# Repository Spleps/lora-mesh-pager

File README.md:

# LoRa mesh-пейджер на власній друкованій платі

Науково-дослідна робота студента групи ЕЛ-12 Батрака Святослава.
Науковий керівник — Качурак Юрій Михайлович. Національний університет «Львівська політехніка», спеціальність G5 «Електроніка».

Текстовий пейджер для зв'язку малої групи без мобільної мережі й інтернету: повідомлення передаються радіо **LoRa на 433 МГц**,
пристрої утворюють **mesh-мережу** (кожен ретранслює чужі повідомлення). Ідея близька до Meshtastic, але апаратна частина —
**власна плата**: ESP32-S3 + голий чип SX1262 з усією обв'язкою, узгодженням і фільтром.

## Стан

| Частина | Стан |
|---|---|
| Принципова схема | готова, ERC — 0 помилок |
| Друкована плата | розведена (4 шари, 60 × 100 мм), DRC — 0 помилок, плата збігається зі схемою; Gerber і файл позицій готові |
| Номінали RF-узгодження | стартові значення розраховано; остаточні — після вимірювань NanoVNA |
| Виготовлення, прошивка | ще не розпочато |

## Що де лежить

| Папка | Вміст |
|---|---|
| [`hardware/v0.5`](hardware/v0.5/README.md) | **поточна версія** плати: проєкт KiCad, PDF схеми, Gerber, BOM, рендери, скрипти |
| [`hardware/v0.4`](hardware/v0.4/README.md) | попередня версія + її [аудит](hardware/v0.4/Аудит%20плати%20v0.4.md) |
| [`hardware/v0.6-plan`](hardware/v0.6-plan/Що%20додати%20в%20плату%20(v0.6).md) | що додати в наступну версію |
| [`docs/01-tema`](docs/01-tema) | пропозиція теми, дослідження по етапах |
| [`docs/02-doslidzhennia`](docs/02-doslidzhennia) | звіт дослідження (аналоги, публікації, розрахунки), джерела, симуляція mesh-мережі |
| [`docs/03-rozrakhunky-rf`](docs/03-rozrakhunky-rf/Стартові%20номінали%20RF%20433%20МГц.md) | розрахунок стартових номіналів радіотракту на 433 МГц |
| [`docs/literatura`](docs/literatura) | список використаних джерел (ДСТУ 8302:2015) |

## Версії плати

| Версія | Що змінилось |
|---|---|
| v0.1–v0.2 | перша схема; схему перемальовано «як вручну», з'єднання звірено нетлистом |
| v0.3 | повна перевірка; виправлено переплутані виводи 4 і 6 RF-ключа PE4259 |
| v0.4 | за джерелами Semtech: режектор 2-ї гармоніки, оновлений ФНЧ, кріпильні отвори |
| **v0.5** | за аудитом: розв'язка ESP32 впритул до виводу живлення, полігон 3,3 В, окреме живлення радіо через феритову намистину, RF-траса без перехідних |
| v0.6 | план: вібромотор, захист акумулятора, роз'єм розширення (ларингофон, GPS), тестові точки |

Кожна папка версії — окремий проєкт KiCad 10: відкривати `lora-pager.kicad_pro` всередині.

## Апаратна частина (v0.5)

- **Радіо:** SX1262 (QFN-24), DC-DC 15 мкГн, TCXO 32 МГц від DIO3, RF-ключ PE4259 від DIO2.
- **RF-тракт 433 МГц:** узгодження підсилювача → ФНЧ 5-го порядку → RF-ключ → LC-балун приймача → π-узгодження антени → SMA.
- **Мікроконтролер:** модуль ESP32-S3-WROOM-1-N16R8 (16 МБ flash, 8 МБ PSRAM, Wi-Fi/BLE, USB).
- **Живлення:** USB-C → заряд Li-ion MCP73831 → автоперемикання USB/батарея → LDO AP2112K-3.3.
- **Інтерфейс:** OLED SSD1306 128×64 (I2C), 3 кнопки, світлодіоди, UART.
- **Плата:** 4 шари (In1 — суцільна земля під RF), 1,6 мм, стек JLC04161H-7628.

## Потужність передавача

Відповідно до переліку радіочастот, що не потребують дозволу (постанова НКЕК № 361 від 03.07.2024, п. 50),
у смузі 433,05–434,79 МГц — 1 мВт ЕВП або до 10 мВт ЕВП при робочому циклі < 10 %.
Плата технічно підтримує до +22 dBm; у прошивці потужність обмежується до +10 dBm.

## Інструменти

KiCad 10, Python 3 + pcbnew API (скрипти в `hardware/*/tools`), Freerouting 2.5 для некритичних цифрових трас
(радіочастина й SPI біля SX1262 розведені вручну), NanoVNA — для налаштування RF (план).

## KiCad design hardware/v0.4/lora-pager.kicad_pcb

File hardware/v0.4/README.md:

# LoRa mesh-пейджер — принципова схема і друкована плата (KiCad 10)

Чернетка v0.4. Відкрити: `lora-pager.kicad_pro` у KiCad. Друк/перегляд: `lora-pager.pdf` (PNG: `lora-pager-schematic-1.png`).

**v0.4 — за первинними джерелами Semtech (AN1200.40, DS SX1268 рис. 14-1):**
- Додано C29 (DNP) паралельно L3 — місце під режектор 2-ї гармоніки, як C4 у схемі Semtech.
- ФНЧ: C17/C19 3,3 → 6,8 пФ, C18 10 → 12 пФ (котушки 22 нГн ті самі). Розрахункове послаблення 2-ї гармоніки 16 → 26 дБ, 3-ї 34 → 46 дБ.
- Додано 4 кріпильні отвори M2,5 без металізації (поза зоною антени модуля ESP32).
- Офіційних номіналів Semtech для 433 МГц у відкритому доступі немає (reference design лише 863–928 МГц) — «TBD 433» підбирати приладом.
  Балун за Semtech: L6 = 0 Ом, на місце C24 — котушка, C25 — конденсатор.
- Плата: DRC 0 помилок, 0 нерозведених, збігається зі схемою.

**v0.3 — повна перевірка проєкту, виправлено помилку:**
- **RF-ключ PE4259: у власному символі були переплутані виводи 4 і 6.** За даташитом pSemi (DOC-03694, табл. 5 і 7)
  вивід 4 = CTRL, вивід 6 = VDD. У v0.1–v0.2 на вивід 4 йшло 3,3 В, а DIO2 — на вивід 6: ключ завжди тримав би
  антену на TX-гілці й приймач не працював би. Тепер DIO2 → R15/C21 → вивід 4, +3V3 → R16/C22 → вивід 6.
  На платі R15/C21 і R16/C22 помінялись місцями, дві траси (DIO2 і відгалуження +3V3) перетрасовано.
- R5 (стягування затвора Q1) 100 кОм → 10 кОм: затвор швидше розряджається після відключення USB, і зворотний
  струм витоку D1 не може тримати Q1 закритим.
- На схемі й шовкографії додано полярність J2 («+», «−», BAT) і примітку про акумулятор із платою захисту.

**v0.2 — схему перемальовано «як руками»:** обв'язка (розв'язувальні C, RC на EN, підтяжки, LED, UART, TCXO, DC-DC)
стоїть біля виводів своєї мікросхеми й з'єднана проводами; мітки лишились тільки на зв'язках між блоками
(SPI/DIO до SX1262, I2C, USB, кнопки, RF-сигнали) та на вузлах RF-тракту. Справа внизу — легенда
(перекреслені елементи = DNP, не паяти). З'єднання v0.2 ті самі, що у v0.1 (звірено нетлистом, 76 цепей).
Перелік елементів: `BOM_draft.csv`. Схему згенеровано скриптом `tools/gen_sch.py`
(`python3 tools/gen_sch.py .` перезапише схему — ручні правки в KiCad тоді зітруться).

ERC: 0 помилок, 1 очікуване попередження (живлення TCXO від виводу DIO3 SX1262).

## Блоки
1. **Живлення**: USB-C (5,1 кОм на CC1/CC2), ESD USBLC6-2SC6, заряд Li-ion MCP73831 (500 мА, R3 = 2 кОм),
   автоперемикання USB/батарея (D1 B5819W + P-MOSFET Q1 AO3401A), вимикач SW1, LDO AP2112K-3.3 (600 мА),
   дільник батареї 1:2 на ADC.
2. **MCU**: ESP32-S3-WROOM-1-N16R8, нативний USB (D+/D-), кнопки RESET/BOOT, UART-роз'єм, зелений LED.
3. **Дисплей**: модуль OLED SSD1306 128×64 I2C (4 виводи). Порядок GND/VCC/SCL/SDA звірити з модулем.
4. **Радіо**: голий SX1262 (QFN-24), DC-DC з дроселем 15 мкГн, VREG 470 нФ, TCXO 32 МГц (TG2520SMN) з
   живленням від DIO3 через 220 Ом + 10 пФ на XTA (за Semtech DS v2.2, рис. 4-2 та 14-2).
5. **RF-тракт 433 МГц**: дросель PA, узгодження PA, ФНЧ 5-го порядку, RF-ключ PE4259 у single-pin режимі
   (вив. 6 VDD = 3,3 В; вив. 4 CTRL ← DIO2: 1 = TX, RFC–RF1; 0 = RX, RFC–RF2), LC-балун приймача, π-узгодження антени, SMA.

## GPIO ESP32-S3
| Сигнал | GPIO | | Сигнал | GPIO |
|---|---|---|---|---|
| LORA_NSS | 10 | | OLED_SDA | 17 |
| LORA_MOSI | 11 | | OLED_SCL | 18 |
| LORA_SCK | 12 | | BTN_UP / DOWN / OK | 4 / 5 / 6 |
| LORA_MISO | 13 | | BAT_ADC | 1 (ADC1_CH0) |
| LORA_BUSY | 14 | | LED_STAT | 2 |
| LORA_DIO1 (IRQ) | 9 | | USB D- / D+ | 19 / 20 |
| LORA_NRST | 8 | | UART TX / RX | 43 / 44 |

Не використано ножки-«страпи» GPIO0/3/45/46 (крім кнопки BOOT на GPIO0) і GPIO35–37 (зайняті PSRAM у N16R8).

## Що ще НЕ готово (обов'язково до замовлення плати)
- **Номінали RF з позначкою `TBD 433`** (L3, C29, C24, L6, C25, L7, C27, C28) — узгодження PA, режектор 2-ї гармоніки, балун RX і антена.
  Підбирати векторним аналізатором (NanoVNA): офіційні reference design Semtech є лише для 863–928 МГц (AN1200.40, табл. 1),
  проєкт для 433 МГц можна запросити в представника Semtech. Елементи з хрестиком = DNP.
- ФНЧ (C17 6,8 пФ, L4 22 нГн, C18 12 пФ, L5 22 нГн, C19 6,8 пФ; конденсатори C0G 2 %) — власний розрахунок, близький до Чебишева 0,1 дБ
  зі зрізом ≈500 МГц, 50 Ом. Вихідний опір PA не 50 Ом, тому після узгодження перевірити спектр гармонік.
- Розрахункове послаблення ФНЧ (ідеальні елементи): 2-га гармоніка (868 МГц) — 26 дБ, 3-тя — 46 дБ; втрати на 434 МГц ≈ 0,6 дБ з реальною добротністю.
  Якщо цього замало — поставити режектор C29 паралельно L3 (резонанс C29–L3 на 868 МГц, як C4 у Semtech AN1200.40, п. 3.1.3).
- У прошивці обов'язково викликати `SetDIO2AsRfSwitchCtrl` — інакше ключ лишиться в положенні RX.
- TCXO: напругу в `SetDIO3AsTCXOCtrl` задати під конкретний TCXO (1,8 В для TG2520SMN-…NM), VBAT ≥ VTCXO + 200 мВ.
- Потужність: в Україні SRD 433,05–434,79 МГц — 1 мВт ЕВП без обмеження робочого циклу або до 10 мВт ЕВП при робочому циклі < 10 % (постанова НКЕК № 361 від 03.07.2024, п. 50, рядок 101; антена «інтегрована/конструктивна»). Не вмикати +22 dBm без дозволу/вимірювань.
- Footprint-и пасивів 0603; для RF можна 0402. Під SX1262 — via під exposed pad, суцільна земля під RF.

## Обмеження конструкції (знати до складання)
- **Акумулятор — тільки із вбудованою платою захисту (PCM).** На платі немає захисту від перерозряду й короткого замикання.
- **Полярність J2 (JST-PH): вивід 1 = «+», вивід 2 = GND.** У готових акумуляторів дроти бувають навпаки — звірити до підключення;
  захисту від переполюсовки немає.
- Заряд 500 мА (R3 = 2 кОм) плюс живлення плати від того ж USB можуть перевищити 500 мА порту USB 2.0; для слабких портів
  і акумуляторів менше 500 мА·год поставити R3 = 3,3–10 кОм (300–100 мА).
- Вимикач SW1 керує входом EN стабілізатора: у вимкненому стані від батареї лишається лише дільник R7/R8 (≈20 мкА).
- Кріпильні отвори M2,5 (без металізації): три в кутах і один біля SMA, усі поза зоною антени ESP32. Біля антени краще пластикові гвинти/стійки.
- 3V3 провалюється, коли батарея нижче ≈3,5 В при великому струмі (падіння на Q1 і LDO) — це нормальна межа розряду.

## Друкована плата v0.4 — розведена
- `lora-pager.kicad_pcb`: 60 × 100 мм, 4 шари, 1,6 мм (JLC04161H-7628):
  F.Cu сигнали + GND-заливка, **In1 = суцільна GND** (опора для RF), In2 = сигнали та +3V3, B.Cu сигнали + GND-заливка.
- **DRC: 0 помилок, 0 нерозведених, плата збігається зі схемою.** Лишились тільки 28 попереджень шовкографії (написи на площадках).
- Класи: Default 0,2 мм / via 0,45/0,2; Power 0,4 мм / via 0,7/0,35; RF 0,35 мм. Біля виводів QFN траси звужуються до 0,12–0,25 мм.
- Виводи SX1262 розведено вручну й закріплено (SPI — два ряди via, RFO/RFI_P/RFI_N короткими трасами, 4 тепловідвідні via),
  решту — Freerouting. ~380 GND-via зшивають заливки з In1.
- Виробництво: `lora-pager-gerbers.zip` (Gerber + свердління), `fab/lora-pager-pos.csv` (координати для монтажу), рендери в `renders/`.

### Як перезібрати
```bash
kicad-cli sch export netlist --format kicadsexpr -o /tmp/pager.net lora-pager.kicad_sch
python3 tools/gen_pcb.py /tmp/pager.net     # розміщення, шари, правила, ручна розводка U2
PASSES=100 tools/route.sh                   # Freerouting -> імпорт -> прибирання хвостів -> зшивка GND
kicad-cli pcb drc --refill-zones --schematic-parity lora-pager.kicad_pcb
```
Якщо змінився лише вигляд схеми, номінали чи примітки (не з'єднання) — плату не перетрасовувати:
```bash
kicad-cli sch export netlist --format kicadsexpr -o route/sch.net lora-pager.kicad_sch
python3 tools/sync_pcb.py                   # нові UUID символів, імена цепей, номінали й примітки; траси без змін
```
Невелика зміна з'єднань: зняти зачеплені траси, оновити цепи площадок і запустити `tools/finish_route.sh`
(дотрасування поверх наявної плати). Приклад — `tools/eco_u6_fix.py` (виправлення PE4259 у v0.3). Додавання елементів без перетрасування —
`tools/eco_v04.py` (C29 і кріпильні отвори у v0.4).
Скрипти перезаписують плату — ручні правки в KiCad після цього зітруться.

### Перед замовленням перевірити
- Номінали RF «TBD 433» (див. вище) і що SMA/антена — 50 Ом.
- Вирівняти написи шовкографії (косметика) та перевірити в KiCad 3D з моделями (на ноутбуці 3D-моделей немає).
- Дросель L1 LPS3010 — наявність; OLED-модуль — порядок виводів GND/VCC/SCL/SDA.

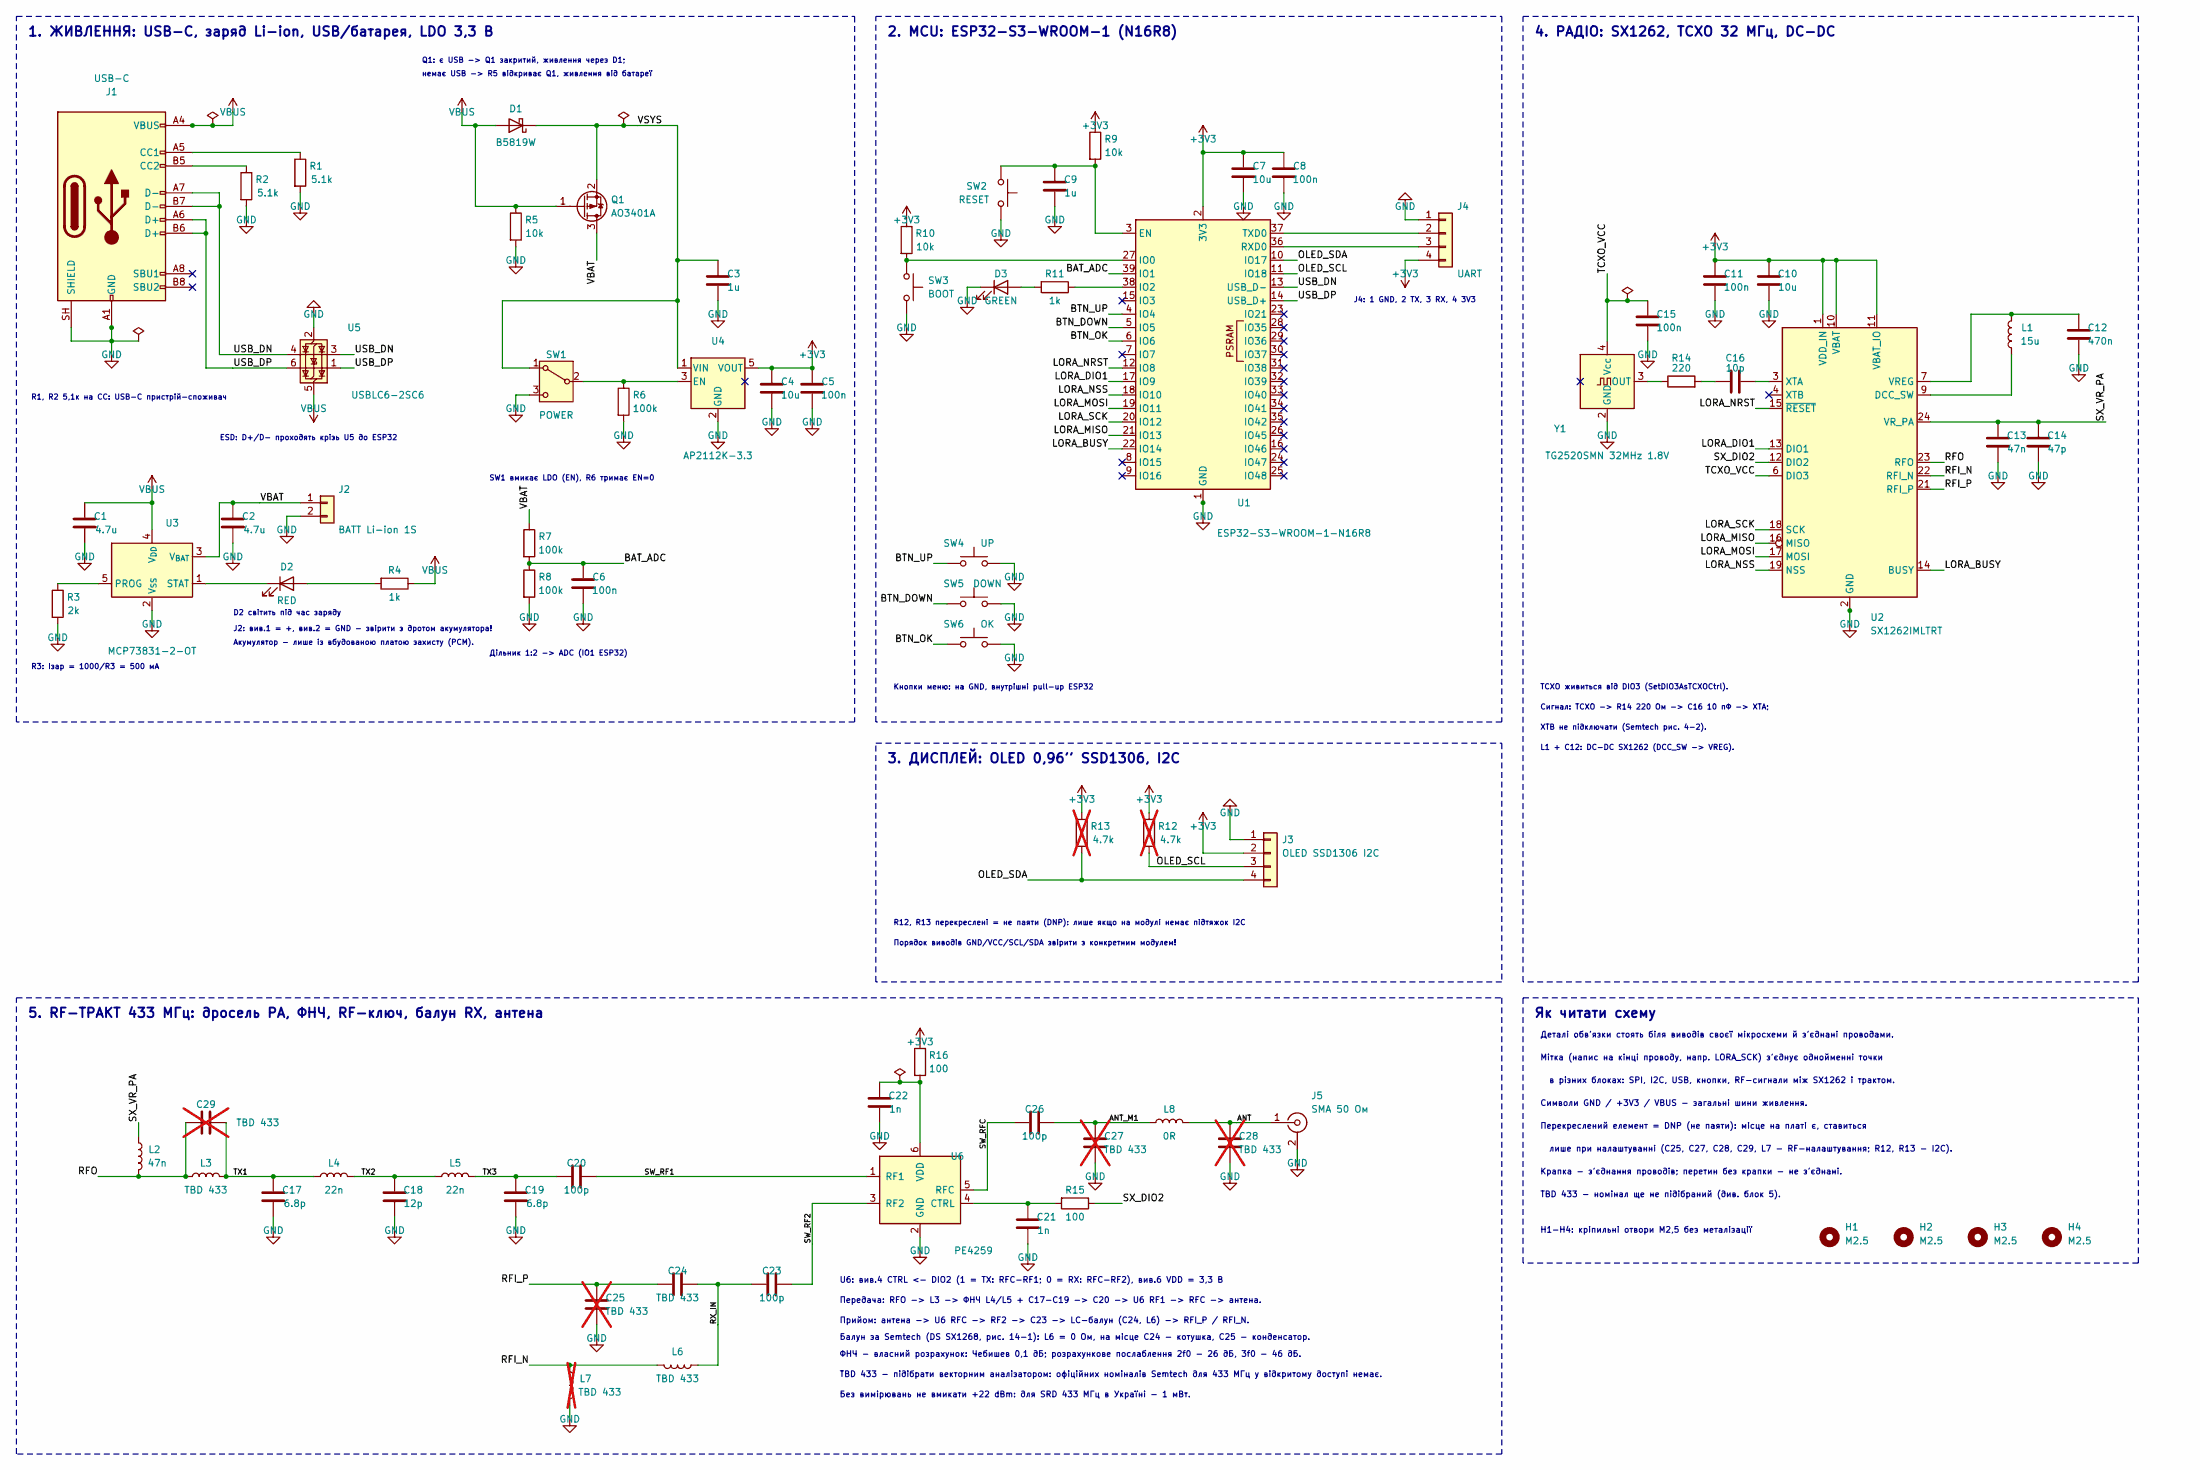
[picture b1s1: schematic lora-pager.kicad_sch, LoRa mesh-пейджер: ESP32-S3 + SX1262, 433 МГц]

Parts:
C1, C2: 4.7u; C_0805_2012Metric
C3, C9: 1u; C_0603_1608Metric
C4, C7, C10: 10u; C_0805_2012Metric
C5, C6, C8, C11, C15: 100n; C_0603_1608Metric
C12: 470n; C_0603_1608Metric
C13: 47n; C_0603_1608Metric
C14: 47p; C_0603_1608Metric
C16: 10p; C_0603_1608Metric
C17, C19: 6.8p; C_0603_1608Metric
C18: 12p; C_0603_1608Metric
C20, C23, C26: 100p; C_0603_1608Metric
C21, C22: 1n; C_0603_1608Metric
C24: TBD 433; C_0603_1608Metric
C25, C27, C28, C29: TBD 433; C_0603_1608Metric; not fitted
D1: B5819W; D_SOD-123
D2: RED; LED_0603_1608Metric
D3: GREEN; LED_0603_1608Metric
H1, H2, H3, H4: M2.5; MountingHole_2.7mm_M2.5
J1: USB-C; USB_C_Receptacle_HRO_TYPE-C-31-M-12
J2: BATT Li-ion 1S; JST_PH_S2B-PH-K_1x02_P2.00mm_Horizontal
J3: OLED SSD1306 I2C; PinHeader_1x04_P2.54mm_Vertical
J4: UART; PinHeader_1x04_P2.54mm_Vertical
J5: SMA 50 Ом; SMA_Amphenol_132289_EdgeMount
L1: 15u; L_Coilcraft_LPS3010
L2: 47n; L_0603_1608Metric
L3, L6: TBD 433; L_0603_1608Metric
L4, L5: 22n; L_0603_1608Metric
L7: TBD 433; L_0603_1608Metric; not fitted
L8: 0R; L_0603_1608Metric
Q1: AO3401A; SOT-23
R1, R2: 5.1k; R_0603_1608Metric
R3: 2k; R_0603_1608Metric
R4, R11: 1k; R_0603_1608Metric
R5, R9, R10: 10k; R_0603_1608Metric
R6, R7, R8: 100k; R_0603_1608Metric
R12, R13: 4.7k; R_0603_1608Metric; not fitted
R14: 220; R_0603_1608Metric
R15, R16: 100; R_0603_1608Metric
SW1: POWER; SW_SPDT_PCM12
SW2: RESET; SW_SPST_TL3342
SW3: BOOT; SW_SPST_TL3342
SW4: UP; SW_SPST_TL3342
SW5: DOWN; SW_SPST_TL3342
SW6: OK; SW_SPST_TL3342
U1: ESP32-S3-WROOM-1-N16R8; ESP32-S3-WROOM-1
U2: SX1262IMLTRT; QFN-24-1EP_4x4mm_P0.5mm_EP2.6x2.6mm
U3: MCP73831-2-OT; SOT-23-5
U4: AP2112K-3.3; SOT-23-5
U5: USBLC6-2SC6; SOT-23-6
U6: PE4259; SOT-363_SC-70-6
Y1: TG2520SMN 32MHz 1.8V; Oscillator_SMD_SeikoEpson_TG2520SMN-xxx-xxxxxx-4Pin_2.5x2.0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

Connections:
+3V3: C4.1, C5.1, C7.1, C8.1, C10.1, C11.1, J3.2, J4.4, R9.1, R10.1, R12.1, R13.1, R16.1, U1.2 (3V3), U2.1 (VDD_IN), U2.10 (VBAT), U2.11 (VBAT_IO), U4.5 (VOUT)
/ANT: C28.1, J5.1 (In), L8.2
/ANT_M1: C26.2, C27.1, L8.1
/BAT_ADC: C6.1, R7.2, R8.1, U1.39 (IO1)
/BTN_DOWN: SW5.1, U1.5 (IO5)
/BTN_OK: SW6.1, U1.6 (IO6)
/BTN_UP: SW4.1, U1.4 (IO4)
/LORA_BUSY: U1.22 (IO14), U2.14 (BUSY)
/LORA_DIO1: U1.17 (IO9), U2.13 (DIO1)
/LORA_MISO: U1.21 (IO13), U2.16 (MISO)
/LORA_MOSI: U1.19 (IO11), U2.17 (MOSI)
/LORA_NRST: U1.12 (IO8), U2.15 (~RESET)
/LORA_NSS: U1.18 (IO10), U2.19 (NSS)
/LORA_SCK: U1.20 (IO12), U2.18 (SCK)
/OLED_SCL: J3.3, R12.2, U1.11 (IO18)
/OLED_SDA: J3.4, R13.2, U1.10 (IO17)
/RFI_N: L6.2, L7.1, U2.22 (RFI_N)
/RFI_P: C24.2, C25.1, U2.21 (RFI_P)
/RFO: C29.1, L2.2, L3.1, U2.23 (RFO)
/RX_IN: C23.2, C24.1, L6.1
/SW_RF1: C20.2, U6.1 (RF1)
/SW_RF2: C23.1, U6.3 (RF2)
/SW_RFC: C26.1, U6.5 (RFC)
/SX_DIO2: R15.1, U2.12 (DIO2)
/SX_VR_PA: C13.1, C14.1, L2.1, U2.24 (VR_PA)
/TCXO_VCC: C15.1, U2.6 (DIO3), Y1.4 (Vcc)
/TX1: C17.1, C29.2, L3.2, L4.1
/TX2: C18.1, L4.2, L5.1
/TX3: C19.1, C20.1, L5.2
/USB_DN: J1.A7 (D-), J1.B7 (D-), U1.13 (USB_D-), U5.3 (I/O2), U5.4 (I/O2)
/USB_DP: J1.A6 (D+), J1.B6 (D+), U1.14 (USB_D+), U5.1 (I/O1), U5.6 (I/O1)
/VBAT: C2.1, J2.1, Q1.3 (D), R7.1, U3.3 (V_{BAT})
/VSYS: C3.1, D1.1 (K), Q1.2 (S), SW1.1 (A), U4.1 (VIN)
GND: C1.2, C2.2, C3.2, C4.2, C5.2, C6.2, C7.2, C8.2, C9.2, C10.2, C11.2, C12.2, C13.2, C14.2, C15.2, C17.2, C18.2, C19.2, C21.2, C22.2, C25.2, C27.2, C28.2, D3.1 (K), J1.A1 (GND), J1.A12 (GND), J1.B1 (GND), J1.B12 (GND), J1.SH (SHIELD), J2.2, J3.1, J4.1, J5.2 (Ext), L7.2, R1.2, R2.2, R3.2, R5.2, R6.2, R8.2, SW1.3 (C), SW2.2, SW3.2, SW4.2, SW5.2, SW6.2, U1.1 (GND), U1.40 (GND), U1.41 (GND), U2.2 (GND), U2.5 (GND), U2.8 (GND), U2.20 (GND), U2.25 (GND), U3.2 (V_{SS}), U4.2 (GND), U5.2 (GND), U6.2 (GND), Y1.2 (GND)
unnamed: C16.1, R14.2
unnamed: D2.2 (A), R4.2
unnamed: D2.1 (K), U3.1 (STAT)
unnamed: D3.2 (A), R11.2
unnamed: J1.A5 (CC1), R1.1
unnamed: J1.B5 (CC2), R2.1
unnamed: J4.2, U1.37 (TXD0)
unnamed: J4.3, U1.36 (RXD0)
unnamed: R6.1, SW1.2 (B), U4.3 (EN)
unnamed: C9.1, R9.2, SW2.1, U1.3 (EN)
unnamed: R10.2, SW3.1, U1.27 (IO0)
unnamed: R11.1, U1.38 (IO2)
unnamed: L1.1, U2.9 (DCC_SW)
unnamed: C12.1, L1.2, U2.7 (VREG)
unnamed: C16.2, U2.3 (XTA)
unnamed: R3.1, U3.5 (PROG)
unnamed: C21.1, R15.2, U6.4 (CTRL)
unnamed: C22.1, R16.2, U6.6 (VDD)
unnamed: R14.1, Y1.3 (OUT)
VBUS: C1.1, D1.2 (A), J1.A4 (VBUS), J1.A9 (VBUS), J1.B4 (VBUS), J1.B9 (VBUS), Q1.1 (G), R4.1, R5.1, U3.4 (V_{DD}), U5.5 (VBUS)

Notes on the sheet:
1. ЖИВЛЕННЯ: USB-C, заряд Li-ion, USB/батарея, LDO 3,3 В
ESD: D+/D- проходять крізь U5 до ESP32
R1, R2 5,1к на CC: USB-C пристрій-споживач
D2 світить під час заряду
J2: вив.1 = +, вив.2 = GND - звірити з дротом акумулятора!
Акумулятор - лише із вбудованою платою захисту (PCM).
R3: Iзар = 1000/R3 = 500 мА
Q1: є USB -> Q1 закритий, живлення через D1;
немає USB -> R5 відкриває Q1, живлення від батареї
U6: вив.4 CTRL <- DIO2 (1 = TX: RFC-RF1; 0 = RX: RFC-RF2), вив.6 VDD = 3,3 В
SW1 вмикає LDO (EN), R6 тримає EN=0
Дільник 1:2 -> ADC (IO1 ESP32)
2. MCU: ESP32-S3-WROOM-1 (N16R8)
J4: 1 GND, 2 TX, 3 RX, 4 3V3
Кнопки меню: на GND, внутрішні pull-up ESP32
3. ДИСПЛЕЙ: OLED 0,96'' SSD1306, I2C
R12, R13 перекреслені = не паяти (DNP): лише якщо на модулі немає підтяжок I2C
Порядок виводів GND/VCC/SCL/SDA звірити з конкретним модулем!
4. РАДІО: SX1262, TCXO 32 МГц, DC-DC
TCXO живиться від DIO3 (SetDIO3AsTCXOCtrl).
Сигнал: TCXO -> R14 220 Ом -> C16 10 пФ -> XTA;
XTB не підключати (Semtech рис. 4-2).
L1 + C12: DC-DC SX1262 (DCC_SW -> VREG).
5. RF-ТРАКТ 433 МГц: дросель PA, ФНЧ, RF-ключ, балун RX, антена
Передача: RFO -> L3 -> ФНЧ L4/L5 + C17-C19 -> C20 -> U6 RF1 -> RFC -> антена.
Прийом: антена -> U6 RFC -> RF2 -> C23 -> LC-балун (C24, L6) -> RFI_P / RFI_N.
Балун за Semtech (DS SX1268, рис. 14-1): L6 = 0 Ом, на місце C24 - котушка, C25 - конденсатор.
ФНЧ - власний розрахунок: Чебишев 0,1 дБ; розрахункове послаблення 2f0 - 26 дБ, 3f0 - 46 дБ.
TBD 433 - підібрати векторним аналізатором: офіційних номіналів Semtech для 433 МГц у відкритому доступі немає.
Без вимірювань не вмикати +22 dBm: для SRD 433 МГц в Україні - 1 мВт.
Як читати схему
Деталі обв'язки стоять біля виводів своєї мікросхеми й з'єднані проводами.
Мітка (напис на кінці проводу, напр. LORA_SCK) з'єднує однойменні точки
в різних блоках: SPI, I2C, USB, кнопки, RF-сигнали між SX1262 і трактом.
Символи GND / +3V3 / VBUS - загальні шини живлення.
Перекреслений елемент = DNP (не паяти): місце на платі є, ставиться
лише при налаштуванні (C25, C27, C28, C29, L7 - RF-налаштування; R12, R13 - I2C).
Крапка - з'єднання проводів; перетин без крапки - не з'єднані.
TBD 433 - номінал ще не підібраний (див. блок 5).
H1-H4: кріпильні отвори M2,5 без металізації

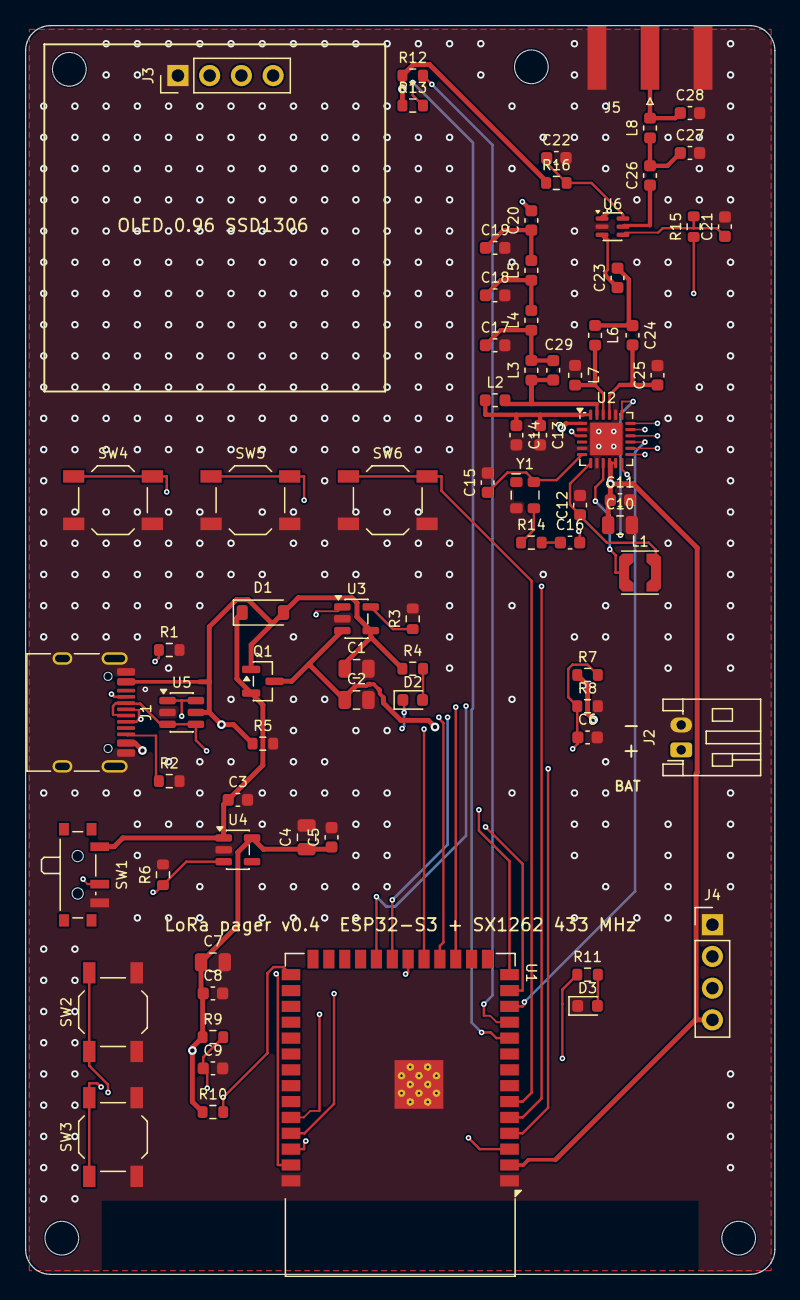
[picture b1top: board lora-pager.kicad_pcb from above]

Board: 4 copper layers, 60.0 x 100.0 mm, 79 parts (0 on the bottom side), 54 nets.

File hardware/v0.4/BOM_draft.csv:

Ref,Value,Footprint,Note
C1,4.7u,Capacitor_SMD:C_0805_2012Metric,
C2,4.7u,Capacitor_SMD:C_0805_2012Metric,
C3,1u,Capacitor_SMD:C_0603_1608Metric,
C4,10u,Capacitor_SMD:C_0805_2012Metric,
C5,100n,Capacitor_SMD:C_0603_1608Metric,
C6,100n,Capacitor_SMD:C_0603_1608Metric,
C7,10u,Capacitor_SMD:C_0805_2012Metric,
C8,100n,Capacitor_SMD:C_0603_1608Metric,
C9,1u,Capacitor_SMD:C_0603_1608Metric,
C10,10u,Capacitor_SMD:C_0805_2012Metric,
C11,100n,Capacitor_SMD:C_0603_1608Metric,біля VBAT/VBAT_IO (Semtech C18)
C12,470n,Capacitor_SMD:C_0603_1608Metric,Semtech C17
C13,47n,Capacitor_SMD:C_0603_1608Metric,
C14,47p,Capacitor_SMD:C_0603_1608Metric,
C15,100n,Capacitor_SMD:C_0603_1608Metric,
C16,10p,Capacitor_SMD:C_0603_1608Metric,
C17,6.8p,Capacitor_SMD:C_0603_1608Metric,"ФНЧ 5 порядку (Чебишев 0,1 дБ, зріз ~500 МГц, 50 Ом), C0G 2%; власний розрахунок"
C18,12p,Capacitor_SMD:C_0603_1608Metric,"ФНЧ, C0G 2%"
C19,6.8p,Capacitor_SMD:C_0603_1608Metric,"ФНЧ, C0G 2%"
C20,100p,Capacitor_SMD:C_0603_1608Metric,розділовий
C21,1n,Capacitor_SMD:C_0603_1608Metric,Semtech C15
C22,1n,Capacitor_SMD:C_0603_1608Metric,Semtech C14
C23,100p,Capacitor_SMD:C_0603_1608Metric,розділовий
C24,TBD 433,Capacitor_SMD:C_0603_1608Metric,LC-балун RX: підбір під 433 МГц
C25,TBD 433,Capacitor_SMD:C_0603_1608Metric,LC-балун RX
C26,100p,Capacitor_SMD:C_0603_1608Metric,розділовий
C27,TBD 433,Capacitor_SMD:C_0603_1608Metric,π-узгодження антени
C28,TBD 433,Capacitor_SMD:C_0603_1608Metric,π-узгодження антени
C29,TBD 433,Capacitor_SMD:C_0603_1608Metric,"режектор 2-ї гармоніки: C29 || L3 резонує на 2f0 = 868 МГц (як C4 у Semtech AN1200.40, п. 3.1.3)"
D1,B5819W,Diode_SMD:D_SOD-123,
D2,RED,LED_SMD:LED_0603_1608Metric,
D3,GREEN,LED_SMD:LED_0603_1608Metric,
J1,USB-C,Connector_USB:USB_C_Receptacle_HRO_TYPE-C-31-M-12,
J2,BATT Li-ion 1S,Connector_JST:JST_PH_S2B-PH-K_1x02_P2.00mm_Horizontal,
J3,OLED SSD1306 I2C,Connector_PinHeader_2.54mm:PinHeader_1x04_P2.54mm_Vertical,
J4,UART,Connector_PinHeader_2.54mm:PinHeader_1x04_P2.54mm_Vertical,
J5,SMA 50 Ом,Connector_Coaxial:SMA_Amphenol_132289_EdgeMount,
L1,15u,Inductor_SMD:L_Coilcraft_LPS3010,"LPS3010-153, DCR<=2 Ом, Idc>=100 мА (Semtech 5.1.5)"
L2,47n,Inductor_SMD:L_0603_1608Metric,дросель живлення PA (як L8 у DATALOGGER02); перевірити для 433
L3,TBD 433,Inductor_SMD:L_0603_1608Metric,"узгодження PA, підбір NanoVNA/за ref-design 433-490"
L4,22n,Inductor_SMD:L_0603_1608Metric,ФНЧ
L5,22n,Inductor_SMD:L_0603_1608Metric,ФНЧ
L6,TBD 433,Inductor_SMD:L_0603_1608Metric,LC-балун RX
L7,TBD 433,Inductor_SMD:L_0603_1608Metric,LC-балун RX
L8,0R,Inductor_SMD:L_0603_1608Metric,π-узгодження: перемичка 0 Ом до налаштування
Q1,AO3401A,Package_TO_SOT_SMD:SOT-23,
R1,5.1k,Resistor_SMD:R_0603_1608Metric,
R2,5.1k,Resistor_SMD:R_0603_1608Metric,
R3,2k,Resistor_SMD:R_0603_1608Metric,Iзар = 1000/R = 500 мА
R4,1k,Resistor_SMD:R_0603_1608Metric,
R5,10k,Resistor_SMD:R_0603_1608Metric,"стягує затвор Q1; 10k, щоб зворотний струм витоку D1 не тримав Q1 закритим"
R6,100k,Resistor_SMD:R_0603_1608Metric,
R7,100k,Resistor_SMD:R_0603_1608Metric,
R8,100k,Resistor_SMD:R_0603_1608Metric,
R9,10k,Resistor_SMD:R_0603_1608Metric,
R10,10k,Resistor_SMD:R_0603_1608Metric,
R11,1k,Resistor_SMD:R_0603_1608Metric,
R12,4.7k,Resistor_SMD:R_0603_1608Metric,"ставити, якщо на модулі немає підтяжок"
R13,4.7k,Resistor_SMD:R_0603_1608Metric,"ставити, якщо на модулі немає підтяжок"
R14,220,Resistor_SMD:R_0603_1608Metric,
R15,100,Resistor_SMD:R_0603_1608Metric,Semtech R3
R16,100,Resistor_SMD:R_0603_1608Metric,Semtech R4
SW1,POWER,Button_Switch_SMD:SW_SPDT_PCM12,
SW2,RESET,Button_Switch_SMD:SW_SPST_TL3342,
SW3,BOOT,Button_Switch_SMD:SW_SPST_TL3342,
SW4,UP,Button_Switch_SMD:SW_SPST_TL3342,
SW5,DOWN,Button_Switch_SMD:SW_SPST_TL3342,
SW6,OK,Button_Switch_SMD:SW_SPST_TL3342,
U1,ESP32-S3-WROOM-1-N16R8,RF_Module:ESP32-S3-WROOM-1,
U2,SX1262IMLTRT,Package_DFN_QFN:QFN-24-1EP_4x4mm_P0.5mm_EP2.6x2.6mm,
U3,MCP73831-2-OT,Package_TO_SOT_SMD:SOT-23-5,
U4,AP2112K-3.3,Package_TO_SOT_SMD:SOT-23-5,
U5,USBLC6-2SC6,Package_TO_SOT_SMD:SOT-23-6,
U6,PE4259,Package_TO_SOT_SMD:SOT-363_SC-70-6,"single-pin режим: вив.6 VDD=3,3 В, вив.4 CTRL=DIO2; CTRL=1 (TX) -> RFC-RF1, CTRL=0 (RX) -> RFC-RF2 (pSemi DOC-03694, табл. 5)"
Y1,TG2520SMN 32MHz 1.8V,Oscillator:Oscillator_SMD_SeikoEpson_TG2520SMN-xxx-xxxxxx-4Pin_2.5x2.0mm,"clipped sine <=1,2 Vpp; напруга = SetDIO3AsTCXOCtrl"
